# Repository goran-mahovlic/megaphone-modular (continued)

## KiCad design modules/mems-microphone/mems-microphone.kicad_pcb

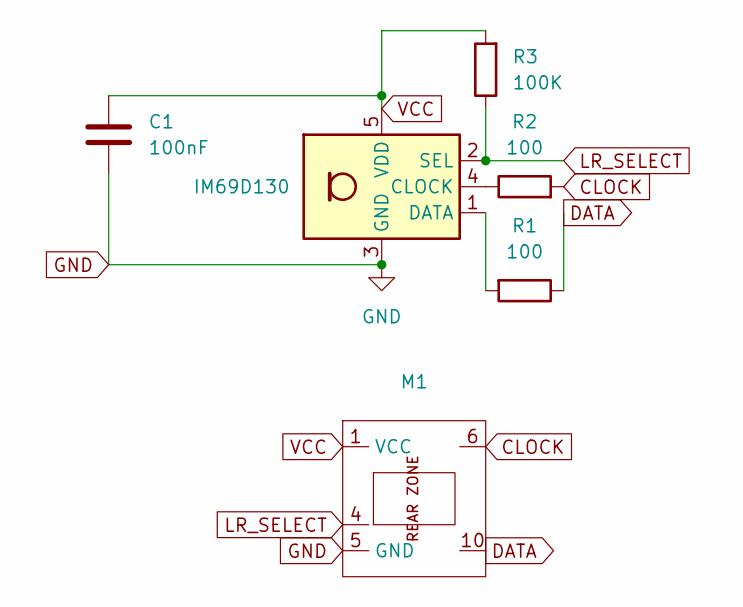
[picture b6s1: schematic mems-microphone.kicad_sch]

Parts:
C1: 100nF; C_1206_3216Metric
M1: MegaCastle2x5-Module-I6.4x7.9-M9C4
MK1: IM69D130; Knowles_LGA-5_3.5x2.65mm
R1, R2: 100; R_0603_1608Metric
R3: 100K; R_0603_1608Metric

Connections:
CLOCK: M1.6, R2.2
DATA: M1.10, R1.1
GND: C1.2, M1.5 (GND), MK1.3 (GND)
LR_SELECT: M1.4, MK1.2 (SEL), R3.1
unnamed: MK1.4 (CLOCK), R2.1
unnamed: MK1.1 (DATA), R1.2
VCC: C1.1, M1.1 (VCC), MK1.5 (VDD), R3.2

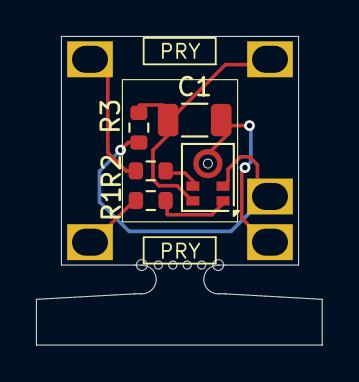
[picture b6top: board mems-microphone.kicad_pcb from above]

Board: 2 copper layers, 15.9 x 17.1 mm, 6 parts (1 on the bottom side), 7 nets.

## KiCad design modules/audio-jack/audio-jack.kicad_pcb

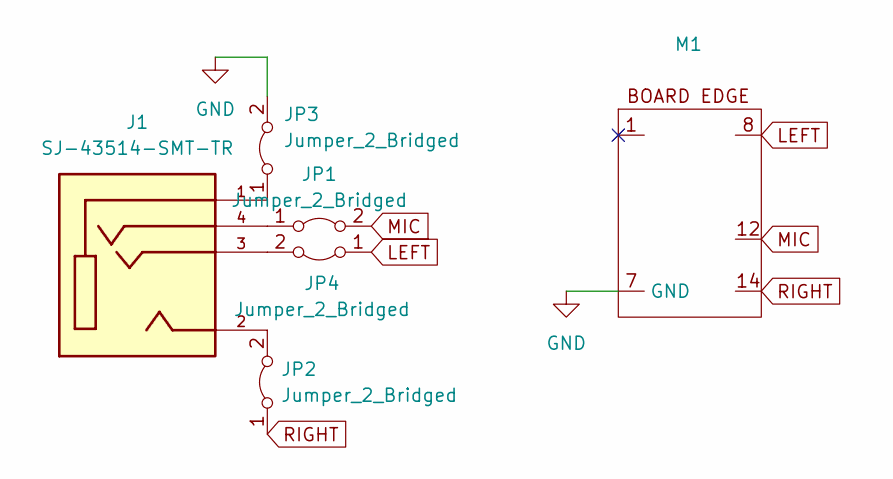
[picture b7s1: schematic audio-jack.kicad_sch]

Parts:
J1: SJ-43514-SMT-TR; CUI_SJ-43514-SMT-TR; PARTREV 1.05
JP1, JP2, JP3, JP4: Jumper_2_Bridged; SolderJumper-2_P1.3mm_Bridged_RoundedPad1.0x1.5mm
M1: MegaCastle2x7-Module-I12.7x13.0-M8314-PANEL-NIBBLE

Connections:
GND: JP3.2 (B), M1.7 (GND)
LEFT: JP4.1 (A), M1.8
MIC: JP1.2 (B), M1.12
unnamed: J1.4, JP1.1 (A)
unnamed: J1.2, JP2.2 (B)
unnamed: J1.1, JP3.1 (A)
unnamed: J1.3, JP4.2 (B)
RIGHT: JP2.1 (A), M1.14

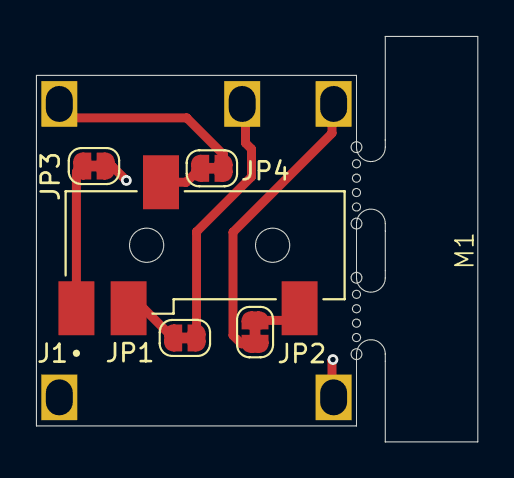
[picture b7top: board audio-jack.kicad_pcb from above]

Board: 2 copper layers, 24.5 x 22.5 mm, 6 parts (0 on the bottom side), 8 nets.

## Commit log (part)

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2024-08-15 add general outline to README
2024-10-01 create footprint for castellated module 2x5
2024-10-03 update footprints etc
2024-10-03 begin working on simple test carrier board
2024-10-03 fix 2x10 wide footprint. add modules to scratch board
2024-10-03 add missing symbol file to repo
2024-10-03 finish adding dummy modules to scratch board
2024-10-04 apply pcbway advice for panels
2025-02-06 add collated requirements from blog post
2025-02-07 update requirements list
2025-02-08 begin working on DC:DC converter module
2025-02-08 begin work on DC:DC converter module schematic
2025-02-08 assign footprints for passives for DC:DC converter module
2025-02-08 add footprints to PCB
2025-02-08 EPAD is pin 21 in footprint
2025-02-08 add 2x11 module symbol and footprint and use for DC:DC module
2025-02-08 rearrange pins etc to keep to 2-layer for DC:DC module
2025-02-08 update board date and rev fields
2025-02-09 relax MPPT charger requirements
2025-02-09 note changes to requirements
2025-02-10 expand module definitions
2025-02-10 add schematic for MEMS module using 2x5 - 4 pins
2025-02-10 add 2x6 -M9C4 module footprint
2025-02-10 add missing files for module footprints
2025-02-11 add footprints for passives for MEMS mic module
2025-02-11 use 0603 resistors to make it all fit
2025-02-11 save changes to mems microphone module
2025-02-11 update and correct 2x5-M9C4 module footprint
2025-02-11 add ADP5301 vreg and work on schematic
2025-02-11 add 1.8V test point
2025-02-11 add remaining passives for audio codec module schematic
2025-02-12 more work on audio codec PCB layout
2025-02-12 finish placing and routing audio codec module
2025-02-13 add footprint and symbol for 3.5mm audio jack
2025-02-13 begin work on 3.5mm audio jack module
2025-02-13 add and update MegaCastle footprints
2025-02-13 fix layers for some measurements in footprints
2025-02-13 finish audio jack module
2025-02-14 procedurally generate pads and component box
2025-02-14 add PRY boxes
2025-02-14 add pry and pad footprint exclusion zones
2025-02-14 add remaining exclusion zones
2025-02-14 get unique variant searching working
2025-02-14 determine suffix name
2025-02-14 add full footprint name to footprint fields
2025-02-14 procedurally place REF** etc
2025-02-14 begin generating module bay footprints
2025-02-14 fix position of GND and VCC bridge silkscreen
2025-02-14 get QR corners right for module bay footprint gen
2025-02-14 add support for EDGE and NOCUTOUT variants of footprints
2025-02-14 add front courtyard and fix edge type footprints
2025-02-15 generate symbol names for insertion
2025-02-15 begin writing symbols to library and moving into place when done
2025-02-15 fix symbol generation errors
2025-02-15 resize pin block and add cut-out indication
2025-02-15 show board edge and cutout / rear zone in symbols
2025-02-15 update MPPT controller
2025-02-15 add additional modules and footprints.
2025-02-17 finish support for panelised module footprints
2025-02-17 add and update module footprints, including -PANELs
2025-02-17 use drill holes for mouse-bites in panelisation
2025-02-19 begin adding support for non-castellated (nibbler) module footprints
2025-02-19 add -NIBBLE footprints for MPPT
2025-02-19 add footprint generation commandline to description field
2025-02-19 update MPPT charge controller
2025-02-19 add more modules to footprint library
2025-02-19 update audio-jack PCB to include panel
2025-02-19 update audio codec module footprint and generate gerbers
2025-02-20 begin work on explicit pin mask setting
2025-02-21 update dc-dc converter footprint
2025-02-21 add more footprints
2025-02-21 add footprints
2025-02-21 update mems microphone module with footprint
2025-02-22 add low-current DC:DC regulator module
2025-02-22 add footprints for low-current DC:DC
2025-02-22 begin work on cellular modem carrier
2025-02-23 add symbol for cellular module holder
2025-02-23 and footprints
2025-02-23 add footprints and symbols for DC:DC regulators
2025-02-23 add 3.3V and 1.8V DC:DC to cellular modem module
2025-02-23 relocate footprints to root dir of module
2025-02-23 add mini pcie connector footprint
2025-02-24 switch to and place MM60 symbols and footprints
2025-02-24 add 3D models for missing components
2025-02-24 add jumpers for isolating 1.8V and 3.3V regulators
2025-02-24 label all pads
2025-02-25 begin work on SIM / SD card module
2025-02-27 update mppt charger submodule
2025-02-28 update module requirements mapping table
2025-02-28 make CSV file actually be CSV
2025-02-28 quote requirements text
2025-02-28 add links to requirements table
2025-02-28 rename and move module requirements reporting page
2025-02-28 add renamed file
2025-03-05 begin working on usb-c power in module
2025-03-05 add symbols and footprints for input power selector components
2025-03-05 add footprints for SMCJ28A. work on reverse polarity protection
2025-03-05 reverse text direction for part labels on DC:DC
2025-03-05 add symbols for 2-pin internal solar panel
2025-03-05 add more footprints etc
2025-03-05 add models etc for more components
2025-03-05 add module outline for input source selecter
2025-03-05 add missing 3D model
2025-03-05 add missing footprints and symbols
2025-03-05 prepare for pcb layout for power selector
2025-03-05 add footprints for MOSFETs for input power selecter
2025-03-05 begin work on battery connector module
2025-03-05 begin work on input power selecter
2025-03-05 finish battery connector module design
2025-03-05 add models for N-channel MOSFET
2025-03-05 fix remaining important DRC violations
2025-03-05 work on battery connector module
2025-03-05 add footprints for DC barrel jack
2025-03-05 work on laying out power input selector
2025-03-05 begin laying out DC input selector
2025-03-10 work on bomtool schematic parser
2025-03-10 fix symbol property parsing
2025-03-10 ignore power symbols
2025-03-10 fix property parsing
2025-03-10 begin making library to track parts
2025-03-10 reduce debug output
2025-03-10 add code to read and write parts library
2025-03-12 work towards automatic digikey parts search
2025-03-12 more work on oauth and digikey search
2025-03-12 get digikey search initially working
2025-03-12 work towards auto-fetching digikey parts
2025-03-22 work on parser for BM83 UART packets
2025-03-23 downgrade requirement 2.1.2 to desirable
2025-03-23 begin work on bluetooth module
2025-03-28 Updating PART NOs
2025-04-01 Adding Mouser parts to power selector
2025-04-01 Adding Mouser parts to sc
2025-04-05 begin work on lcd panel modeul
2025-04-05 update bluetooth module
2025-04-05 more work on bt monitor test program
2025-04-05 add footprints etc for LCD cable connectors
2025-04-25 use rounded rect for spare pads
2025-04-25 fix sparepad footprint problems
2025-04-25 sparepad now a footpring option
2025-04-25 update offset of spare hole for pads
2025-04-25 fix compiler warning and catch file creation errors
2025-04-25 use much more efficient combination selection algorithm.
2025-04-25 stop munging module size
2025-04-28 Adding cellular modem footprints
2025-04-30 KiCad v9 adding new footprints
2025-04-30 Updating high-efficiency_dc-dc_converter
2025-04-30 Updating USB-Power-IN
2025-04-30 Updating footprint on input power selector
2025-04-30 Removing not needed lck files
2025-05-01 Updating audio-codec
2025-05-01 Updating cellular-modem
2025-05-25 update LCD module
2025-05-25 begin writing tool to convert OTF to megaphone fonts
2025-05-25 more work on OTF to bitmap font converter
2025-06-16 fix some draw_glyph bugs
2025-06-16 update unicode font test program
2025-06-16 implement writing to screen and colour RAM
2025-06-16 update mega65-libc to get fixed shread()
2025-06-16 work around first row of text top pixel glitch
2025-06-16 begin generating FCM pixel data for fonts
2025-06-16 add mega65-libc to .gitmodules
2025-06-16 add generator for attribute tables
2025-06-16 add note for downloading Noto emoji and text fonts
2025-06-16 enable alpha compositor. debug glyph display problems
2025-06-16 add symlinks to pick out TTFs from Noto font archive
2025-06-16 progress towards properly rendering interlaced FCM unicode glyphs
2025-06-16 begin working on test program for unicode font handling
2025-06-16 begin implementing glyph cache
2025-06-16 use shopen() to cat text file
2025-06-16 add script to convert twitter emojis
2025-06-16 implement colour cube setup functions
2025-06-16 add mega65-libc as sub-module for telephony software
2025-06-16 progress towards unicode glyph rendering
2025-06-16 enable VIC-III attrs to allow alternate palette selection
2025-06-16 use shseek() in dummy test
2025-06-16 implement creating MEGA65 pre-rendered fonts
2025-06-16 implement iterating over whole font
2025-07-28 fix end-of-file chain
2025-07-28 add code to test sector ordering
2025-07-28 fix fseek() arg order. Get provision writing full structure
2025-07-28 more work on telephony provisioning utility
2025-07-28 more work towards phone provisioning utility
2025-07-28 more work on UTF-8 Unicode string printer
2025-07-28 begin implementing d81 manipulation code
2025-07-28 begin work on UTF-8 parsing
2025-07-28 fix bugs in D81 formatting
2025-07-28 begin ork on SMS/contact stimulator
2025-07-30 timestamps relative to aztec calendar in sms stim
2025-07-30 fix compilation errors
2025-07-30 remove unused var
2025-07-30 setup record numbers in disk images
2025-07-30 work on importing contacts and messages
2025-07-31 fix mounting of contact0.d81 and updating BAM after record allocate
2025-07-31 debug various problems with record and contact management
2025-07-31 tidy up debug output. Prepare for message import
2025-08-01 more work towards sortind disk images
2025-08-01 get d81 sort code to compile. not yet working
2025-08-01 fix compiler warning
2025-08-01 create sorted versions of contacts after populating
2025-08-01 put work buffer somewhere sensible for linux
2025-08-01 fix logic errors in sort
2025-08-01 create sort D81 for contact by phone number
2025-08-02 fix reading contacts
2025-08-02 fix available sectors per disk
2025-08-02 work towards indexing D81s
2025-08-02 refactor out slab geometry. Support writing slabs
2025-08-02 set/clear index bits
2025-08-02 work on generating indexes
2025-08-02 use shared buffer union for sort
2025-08-02 add missing include for import
2025-08-02 more work on indexing
2025-08-02 make include files reentrant
2025-08-02 factor include path out
2025-08-02 move record read/write out of contacts.c
2025-08-02 use renamed record read/write routines
2025-08-02 fix bug introduced with slab_read() refactor
2025-08-02 report sort failures
2025-08-02 debug code for slab_read
2025-08-02 actually map chars to mod(56) for indexing
2025-08-02 fix more index page generation logic errors
2025-08-03 more progress on search
2025-08-03 more work on search and search test utility
2025-08-03 implement filtering of search results
2025-08-03 show search results
2025-08-03 work towards find contact by number
2025-08-03 add utility function for querying by whole string
2025-08-03 search for contact goes in search.
2025-08-03 begin work on sms handling functions
2025-08-03 get it compiling again with sms.c
2025-08-03 progress towards sms import
2025-08-03 update message thread index when receiving an SMS
2025-08-03 get multiple SMS rx working
2025-08-03 use fail() to report and log errors across all modules
2025-08-03 make sure we're in the right directory before sort_d81 calls
2025-08-03 show export result in test target
2025-08-03 implement import and logging of SMS TX events
2025-08-03 finish fixing search by phone number on sms_log()
2025-08-03 create index of all contact fields
2025-08-03 fix logic errors with re-running queries when stale
2025-08-03 fix contact search management
2025-08-03 only put sector markers in contacts D81s
2025-08-03 allow search to show messages
2025-08-03 don't put sector markers in non-CONTACTS D81s
2025-08-04 start work on TE0725 carrier
2025-08-04 add 2x25 headers to TE0725 carrier module
2025-08-04 add wider footprint for TE0725 carrier
2025-08-04 and even wider module for TE0725
2025-08-11 MegaCastle symbol update
